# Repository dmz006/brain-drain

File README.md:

# brain-drain

A standalone disk sanitizer: plug a drive in, it gets wiped to NIST SP 800-88 Rev. 2 and you get a certificate. No buttons, no
screen to poke at, no PC. A Raspberry Pi Compute Module 5 on a custom carrier board, plug-in bay cards (one per drive, up to eight, four
in version 1), an M.2 NVMe bay, a Python service and a 3D-printed enclosure that fits a backpack.

> **Status: design complete enough for layout review, nothing fabricated yet.** Both boards are routed with 0 DRC errors in KiCad, the
> software has 74 passing tests and the enclosure exports clean STLs. The boards have not been reviewed by a board designer and nothing has
> been simulated; the first bench test with a real drive is scheduled for 2026-09-26. See [docs/STATUS.md](docs/STATUS.md).
> **Handing this to an engineer? Start with [docs/LAYOUT-REVIEW.md](docs/LAYOUT-REVIEW.md).**

## What it does

* Up to eight SATA bays as plug-in cards (four fitted), each a USB 3 bridge
  with its own switched power. Drives are not docked: each bay is a 0.5 m
  22-pin SATA cable (data + power) that rises through the lid and plugs straight
  onto a bare 3.5" or 2.5" drive lying on the bench. Plus an M.2 NVMe bay under
  the lid (bay 9). Each bay is independent.
* Set the policy on an 8-way DIP switch. Plug a drive in: it is identified,
  wiped, verified and reported. Unplug it: the job aborts. That is the whole UI.
* Methods follow NIST 800-88 Rev. 2: single-pass overwrite with full
  verification for magnetic drives, firmware Sanitize (crypto or block erase)
  for SSDs and NVMe, legacy 3-pass and 7-pass available for those who insist.
* A JSON certificate per drive per job: what was attempted, what worked, how it
  was verified, and which tier (Clear / Purge) is honestly claimed.
* A 128×64 OLED shows per-bay progress and ETA. When idle it shows a QR code:
  scan it with a phone to join the unit's Wi-Fi, open the address, and you get
  the status page, the certificates to download, the log, and the option to
  join the unit to your own network. A key on the screen authorises changes.
  DIP mode 110 resets Wi-Fi (or everything, with DIP 8) without a network.

## Use cases

* IT refresh: wiping a pile of decommissioned laptop and desktop drives
  unattended, four at a time, with paperwork for each.
* Reselling or donating hardware where a Purge-level record is wanted.
* Small MSPs and repair shops that need a repeatable wipe without dedicating a PC.

## The hardware

|  |  |
|---|---|
| **Brain board**, 150 x 122 mm, six layers: CM5 wireless, two USB5744 hubs, eight PCIe-x1-style bay slots, M.2 socket, 12 V input and bucks, OLED, DIP switch | **Bay card**, 45 x 46 mm, four layers: ASM1153E USB 3 to SATA bridge, per-bay 12 V / 5 V power switch, SATA receptacle, PCIe x1 fingers |

More views, the case, the assembled unit, an exploded view, a cut-away and the complete system: [docs/RENDERS.md](docs/RENDERS.md).

## Repository layout

| Directory | Workstream | State |
|---|---|---|
| [`hardware/`](hardware/README.md) | KiCad 9 projects for the brain board and the bay card, generated from one netlist source; review pack, per-layer images, BOM | schematic clean; both boards routed, 0 open connections, 0 DRC errors, all differential pairs matched; **unreviewed, unsimulated, not fabricated** |
| [`software/`](software/README.md) | `braindrain` Python service, simulator, bench tool, Wi-Fi access point + phone page, Pi deployment | 74 tests, ready for the first bench |
| [`enclosure/`](enclosure/README.md) | OpenSCAD case, about 157 x 145 x 62 mm: tray, hinged lid with eight cable windows and a snap latch, OLED bezel; render gallery script | STLs export, renders done, not printed |
| [`docs/`](docs/README.md) | architecture, review guide, BOM, decisions, status, usage, diagrams, renders | |

## Quick start

```
# simulate the appliance on any Linux box
cd software && python3 -m venv .venv && . .venv/bin/activate && pip install -e ".[dev]"
braindrain simulate --grace 2            # terminal 1
braindrain sim-plug 1 --size 1G --prefill # terminal 2: a drive appears in bay 1 and is wiped

# regenerate a board from its source and route it unattended (BD_PROJECT=brain or card; see docs/USAGE.md)
cd hardware && python3 tools/symgen.py && BD_PROJECT=card python3 tools/gen_sch.py && BD_PROJECT=card sh tools/route_full.sh

# export the enclosure and render every image
cd enclosure && make && make renders
```

More in [docs/USAGE.md](docs/USAGE.md).

## Documentation

* **For the layout engineer: [Layout and design review guide](docs/LAYOUT-REVIEW.md)** · generated review data in [`hardware/review/`](hardware/review/)
* [Architecture](docs/ARCHITECTURE.md) · [System block diagram](docs/img/system-block.png) · [Renders and drawings](docs/RENDERS.md)
* [Bill of materials](docs/BOM.md) · [Fabrication and assembly vendors, cost estimate](docs/FABRICATION.md) · [Decisions](docs/DECISIONS.md)
* [Status and remaining work](docs/STATUS.md) · [Testing tracker](docs/testing-tracker.md)
* [Usage and regeneration](docs/USAGE.md) · [Bench plan for 2026-09-26](docs/saturday-bench-plan.md)
* [BRAIN-DRAIN-CONTEXT.md](BRAIN-DRAIN-CONTEXT.md) project context · [AGENT.md](AGENT.md) rules for agents and contributors · [CONTRIBUTING](CONTRIBUTING.md) · [CHANGELOG](CHANGELOG.md)

## Safety

This device destroys data by design. The software's safety fence only ever
targets whole disks behind an allow-listed USB bridge on a configured bay port,
or the M.2 slot, and never anything mounted or holding the root filesystem.
Treat every drive that touches a bay as gone.

## Licence

[Polyform Noncommercial 1.0.0](LICENSE): you may use, modify and share this
project for noncommercial purposes. Commercial use needs permission from the
author. Applies to the hardware sources, the software and the enclosure alike.

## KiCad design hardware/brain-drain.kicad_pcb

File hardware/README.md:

# hardware: the brain board and the bay card

Two KiCad 9 projects, both **generated** from `tools/design.py` (see [../docs/LAYOUT-REVIEW.md](../docs/LAYOUT-REVIEW.md) for how, and for what a
layout engineer must check). Design intent: [../docs/ARCHITECTURE.md](../docs/ARCHITECTURE.md) section 3. Parts: [../docs/BOM.md](../docs/BOM.md).
Regenerate and route commands: [../docs/USAGE.md](../docs/USAGE.md).

| | Brain board | Bay card |
|---|---|---|
| Project | `brain-drain.kicad_pro` | `bay-card/bay-card.kicad_pro` |
| Size, layers | 150 x 122 mm, 6 layers (F sig, In1 GND, In2 sig, In3 sig, In4 power, B sig), 1.6 mm, ENIG | 45 x 46 mm, 4 layers (F sig, In1 GND, In2 power, B sig), 1.6 mm, ENIG, finger tab |
| Contents | CM5 wireless, two USB5744 hubs, eight PCIe x1 bay slots, M.2 socket, 12 V input and bucks, OLED and DIP headers, LEDs, microSD, USB-C | ASM1153E bridge, two P-FET power switches with PTC fuses, SATA 22-pin receptacle, PCIe x1 fingers |
| Schematic sheets | `power-input`, `power-bucks`, `cm5`, `usb3-hub-A`, `usb3-hub-B`, `bay-slots`, `m2-nvme` | `bridge`, `bay-switch`, `edge` |
| Status | routed: 0 open connections, 0 DRC errors, 44 pairs matched | routed: 0 open connections, 0 DRC errors, 8 pairs matched |

More views and the assembled unit: [../docs/RENDERS.md](../docs/RENDERS.md). KiCad's own 3D views are in `renders/`, one image per layer in
`renders/layers/` (F.Cu, In1 to In4, B.Cu, assembly-top, assembly-bottom, mask), schematic sheets in `renders/schematic/`.

## Layout of this directory

```
hardware/
  brain-drain.kicad_pro / .kicad_sch / .kicad_pcb   the brain (generated; the PCB also carries the routing)
  sheets/*.kicad_sch                                7 brain sheets (generated)
  bay-card/                                         the bay card project, same layout: .kicad_pro/.sch/.pcb, sheets/, routing/, renders/
  CONNECTIONS.md, bay-card/CONNECTIONS.md           net-by-net connection lists (generated)
  lib/brain-drain.kicad_sym, lib/brain-drain.pretty custom symbols and footprints (see lib/brain-drain.pretty/README.md for origins)
  review/                                           generated review pack: design rules, stack-up, planes, keep-outs, routing statistics,
                                                    DRC / ERC summaries, footprint provenance, netlists, placement CSV, schematic PDFs
  routing/, bay-card/routing/                       Specctra DSN/SES for freerouting, drc.json, open.md, pairs.md, chain.log
  renders/, bay-card/renders/                       KiCad 3D views, per-layer PNGs, schematic PNGs and PDFs
  bom/                                              brain-drain-bom.csv, bay-card-bom.csv (generated)
  ref/                                              pin tables (CSV), DOWNLOADS.md; ref/datasheets/ is gitignored
  tools/                                            the generators and the routing pipeline, listed in ../docs/LAYOUT-REVIEW.md section 6
  fab/                                              fab/<date>/ order packs (gitignored)
```

## Board rules

* Design rules follow the Raspberry Pi CM5IO reference: 0.13 mm tracks, 0.125 mm clearance, 0.45/0.2 mm vias, 0.3 mm copper to the board edge,
  0.2 mm hole clearance; power nets 0.3 mm tracks with 0.6/0.3 mm vias; 0.3/0.15 mm vias for the 0.4 mm-pitch QFN supply pins only (D8, confirm
  with the fab). They are written into each project file by `route.py prepare`; the table is in `review/design-rules.md`.
* Differential pairs: 90 ohm (USB 3, SATA, USB 2), 85 ohm (PCIe). The class `DiffPair90` is 0.147 mm / 0.253 mm gap, **carried over from a four-layer
  design and not yet recalculated for the six-layer stack-up**. Pairs are length-matched end to end (across the series capacitors) to 0.15 mm.
* CM5 antenna strip: no copper on any layer and no parts (rule area `keepout_CM5_antenna`); keep-outs around the CM5's four standoff holes.
* CM5 boot-order straps: eMMC/SD only. All bay power switches default **off** (10 k pull-down on `BAY_EN`, on the card).
* Input: 4-pin DIN (Kycon KPJX-4S-S); the pin assignment must match the chosen brick.

## Before fabrication

See [../docs/LAYOUT-REVIEW.md](../docs/LAYOUT-REVIEW.md) (priority items and the sign-off checklist) and [../docs/STATUS.md](../docs/STATUS.md) R2, R3, R10, R25 to R30:
the stack-up and pair geometry, the M.2 footprint against the TE drawing, the Molex face position, the DIN pinout from the chosen brick, test points, fiducials
and ESD, the card panel.

## Bench validation that does not need these boards

Any Linux box plus an ASM1153E-based USB dock answers the risky questions: does `hdparm --sanitize-*` pass through, does the bridge survive a long SECURITY ERASE,
does `--sanitize-status` report progress. A Pi 5 with two docks is the exact software test bed for this topology. Do this first
([../docs/saturday-bench-plan.md](../docs/saturday-bench-plan.md)).

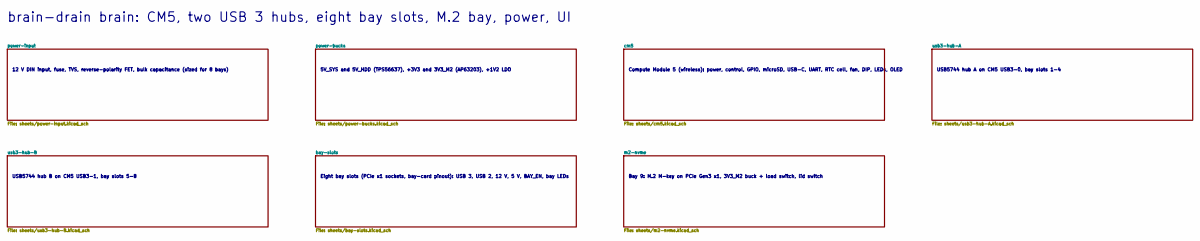
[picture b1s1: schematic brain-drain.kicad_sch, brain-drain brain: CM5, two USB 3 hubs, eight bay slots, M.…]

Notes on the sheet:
brain-drain brain: CM5, two USB 3 hubs, eight bay slots, M.2 bay, power, UI
12 V DIN input, fuse, TVS, reverse-polarity FET, bulk capacitance (sized for 8 bays)
5V_SYS and 5V_HDD (TPS56637), +3V3 and 3V3_M2 (AP63203), +1V2 LDO
Compute Module 5 (wireless): power, control, GPIO, microSD, USB-C, UART, RTC cell, fan, DIP, LEDs, OLED
USB5744 hub A on CM5 USB3-0, bay slots 1-4
USB5744 hub B on CM5 USB3-1, bay slots 5-8
Eight bay slots (PCIe x1 sockets, bay-card pinout): USB 3, USB 2, 12 V, 5 V, BAY_EN, bay LEDs
Bay 9: M.2 M-key on PCIe Gen3 x1, 3V3_M2 buck + load switch, lid switch

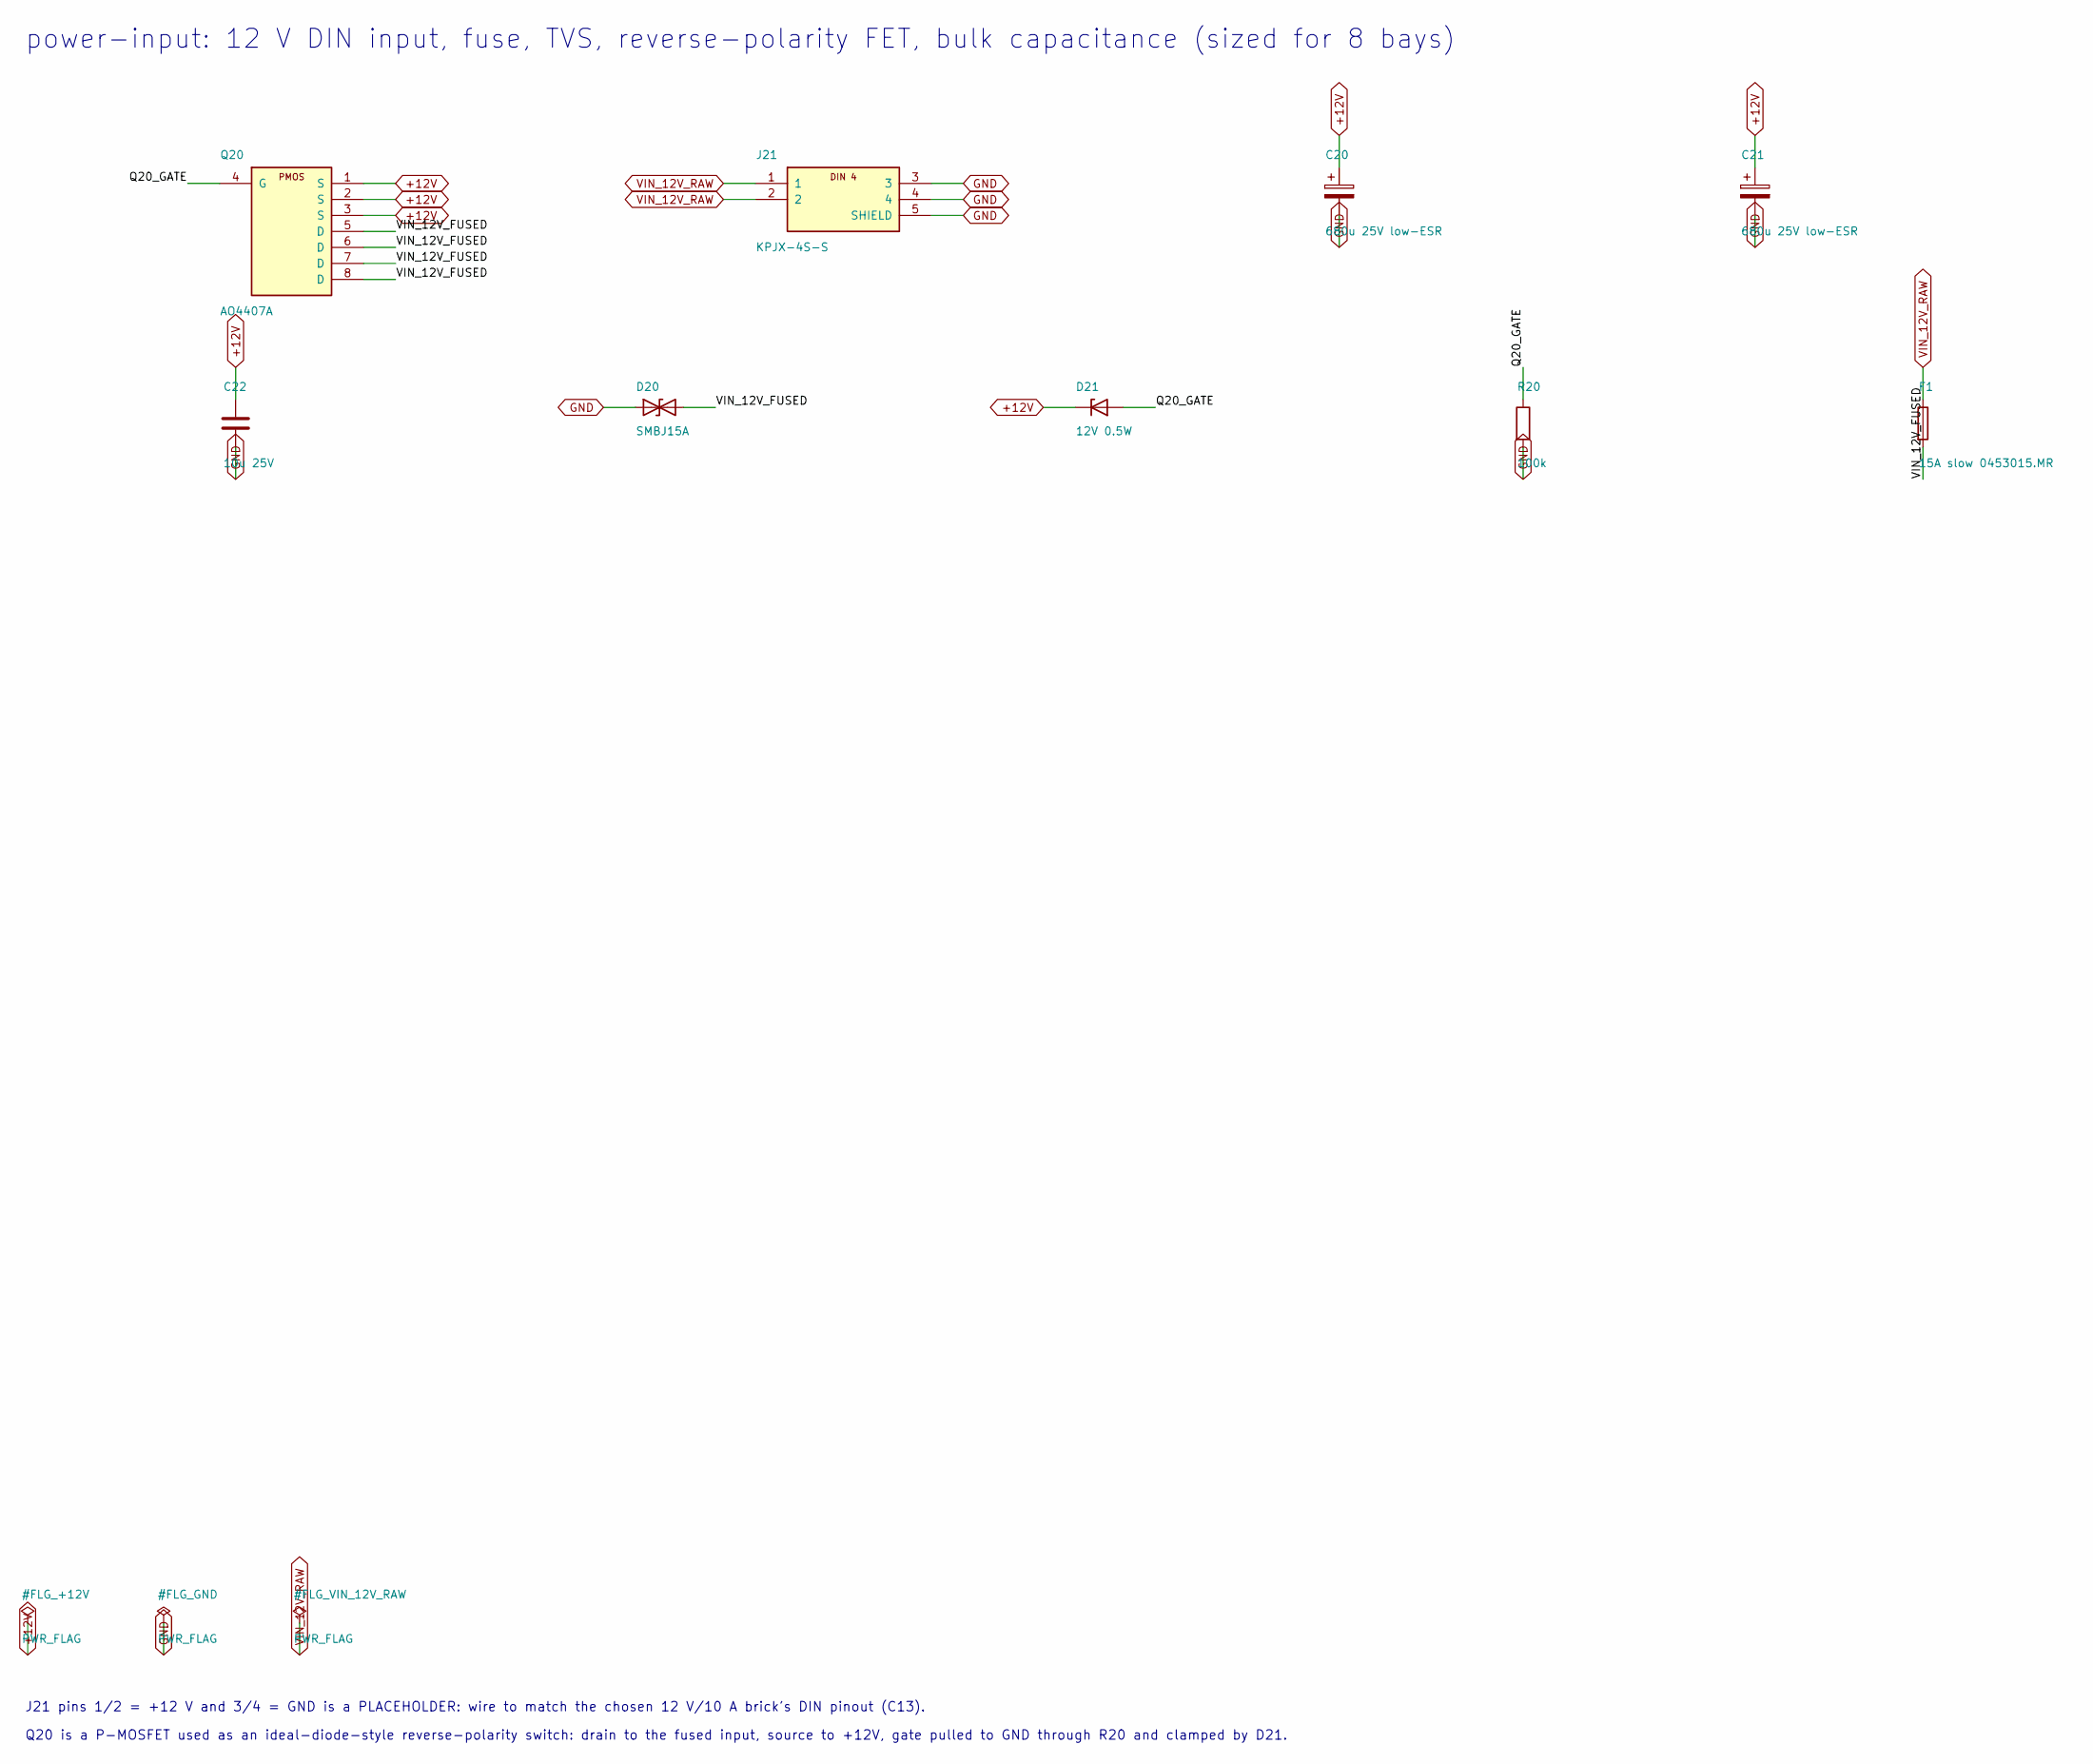
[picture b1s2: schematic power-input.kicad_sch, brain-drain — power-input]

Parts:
C20, C21: 680u 25V low-ESR; CP_Elec_10x10.5
C22: 10u 25V; C_1210_3225Metric
D20: SMBJ15A; D_SMB
D21: 12V 0.5W; D_SOD-123
F1: 15A slow 0453015.MR; Fuse_Littelfuse-NANO2-451_453
J21: KPJX-4S-S; Kycon_KPJX-4S-S
Q20: AO4407A; SOIC-8_3.9x4.9mm_P1.27mm
R20: 100k; R_0603_1608Metric

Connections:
+12V: C20.1, C21.1, C22.1, D21.1 (K), Q20.1 (S), Q20.2 (S), Q20.3 (S); also elsewhere on the board
GND: C20.2, C21.2, C22.2, D20.1 (A1), J21.3, J21.4, J21.5 (SHIELD), R20.2; also elsewhere on the board
Q20_GATE: D21.2 (A), Q20.4 (G), R20.1
VIN_12V_FUSED: D20.2 (A2), F1.2, Q20.5 (D), Q20.6 (D), Q20.7 (D), Q20.8 (D)
VIN_12V_RAW: F1.1, J21.1, J21.2

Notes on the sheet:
power-input: 12 V DIN input, fuse, TVS, reverse-polarity FET, bulk capacitance (sized for 8 bays)
J21 pins 1/2 = +12 V and 3/4 = GND is a PLACEHOLDER: wire to match the chosen 12 V/10 A brick's DIN pinout (C13).
Q20 is a P-MOSFET used as an ideal-diode-style reverse-polarity switch: drain to the fused input, source to +12V, gate pulled to GND through R20 and clamped by D21.

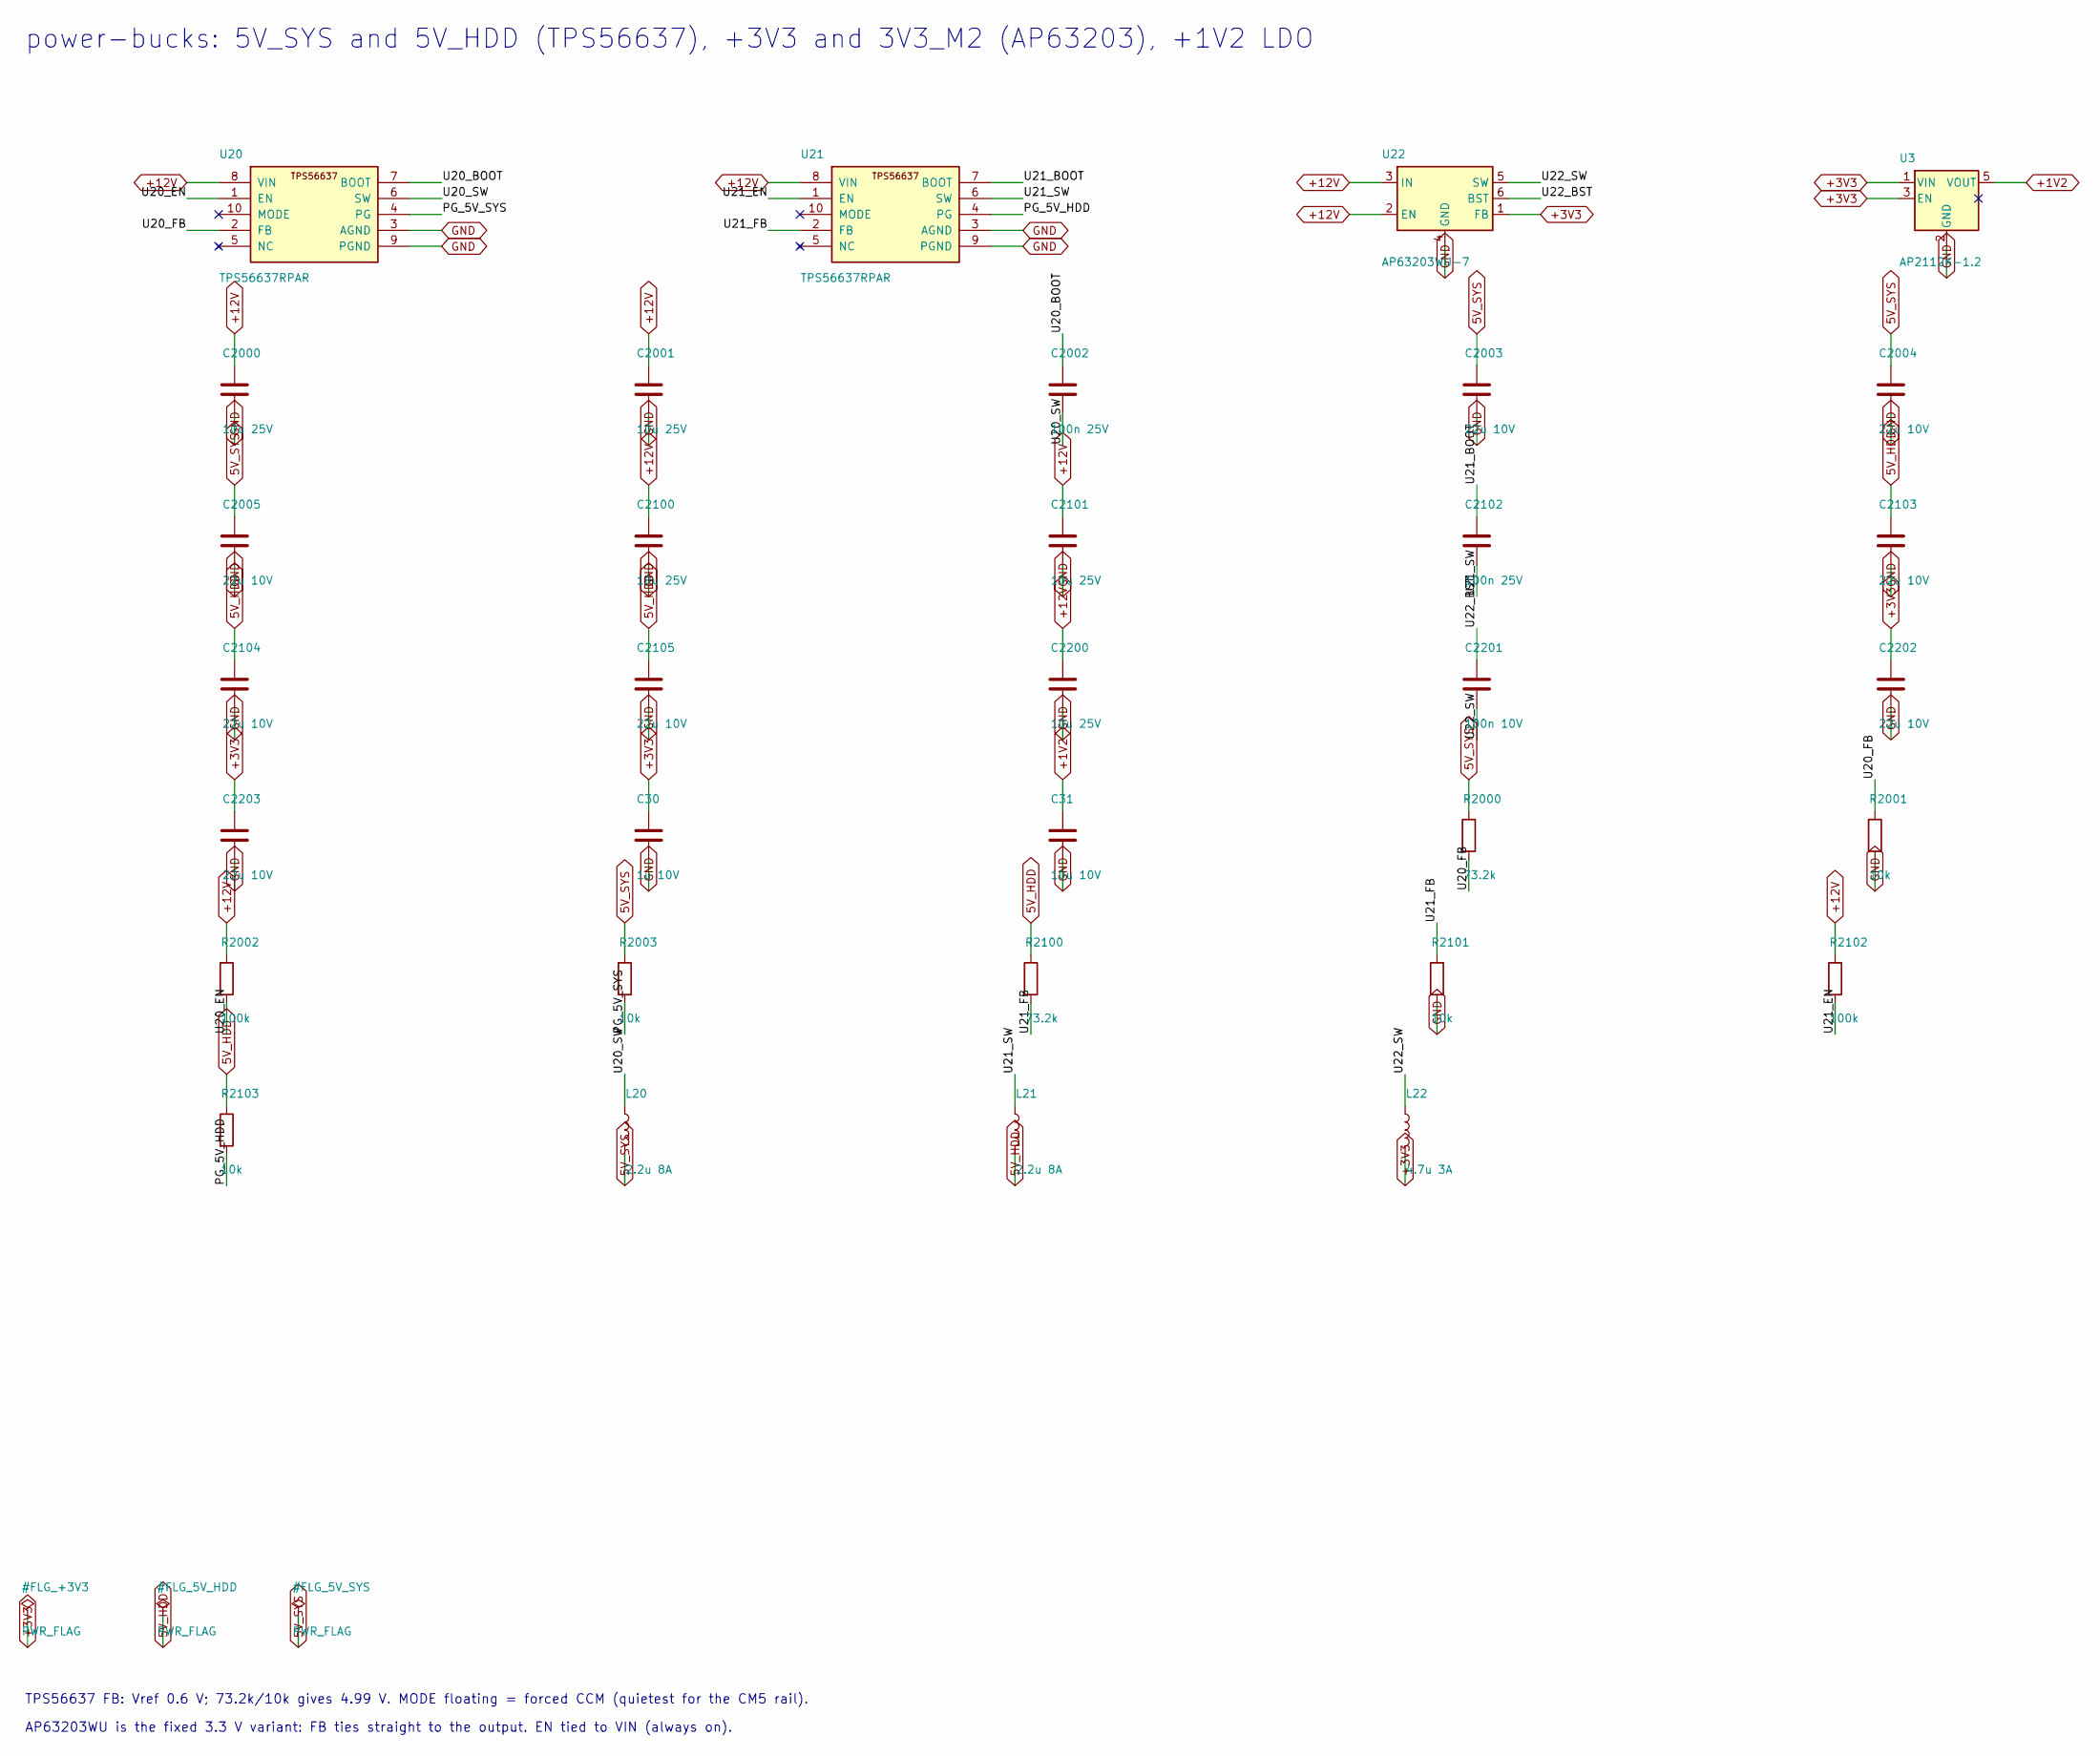
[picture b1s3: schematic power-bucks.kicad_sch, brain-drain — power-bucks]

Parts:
C30: 1u 10V; C_0402_1005Metric
C31: 10u 10V; C_0805_2012Metric
C2000, C2001, C2100, C2101, C2200: 10u 25V; C_1210_3225Metric
C2002, C2102: 100n 25V; C_0402_1005Metric
C2003, C2004, C2005, C2103, C2104, C2105, C2202, C2203: 22u 10V; C_0805_2012Metric
C2201: 100n 10V; C_0402_1005Metric
L20, L21: 2.2u 8A; L_Taiyo-Yuden_NR-60xx
L22: 4.7u 3A; L_Taiyo-Yuden_NR-40xx
R2000, R2100: 73.2k; R_0402_1005Metric
R2001, R2003, R2101, R2103: 10k; R_0402_1005Metric
R2002, R2102: 100k; R_0402_1005Metric
U3: AP2112K-1.2; SOT-23-5
U20, U21: TPS56637RPAR; Texas_RPA0010A_VQFN-HR-10_3x3mm
U22: AP63203WU-7; TSOT-23-6

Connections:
5V_HDD: C2103.1, C2104.1, C2105.1, L21.2, R2100.1, R2103.1; also elsewhere on the board
5V_SYS: C2003.1, C2004.1, C2005.1, L20.2, R2000.1, R2003.1; also elsewhere on the board
+1V2: C31.1, U3.5 (VOUT); also elsewhere on the board
+3V3: C30.1, C2202.1, C2203.1, L22.2, U3.1 (VIN), U3.3 (EN), U22.1 (FB); also elsewhere on the board
+12V: C2000.1, C2001.1, C2100.1, C2101.1, C2200.1, R2002.1, R2102.1, U20.8 (VIN), U21.8 (VIN), U22.2 (EN), U22.3 (IN); also elsewhere on the board
GND: C30.2, C31.2, C2000.2, C2001.2, C2003.2, C2004.2, C2005.2, C2100.2, C2101.2, C2103.2, C2104.2, C2105.2, C2200.2, C2202.2, C2203.2, R2001.2, R2101.2, U3.2 (GND), U20.3 (AGND), U20.9 (PGND), U21.3 (AGND), U21.9 (PGND), U22.4 (GND); also elsewhere on the board
PG_5V_HDD: R2103.2, U21.4 (PG)
PG_5V_SYS: R2003.2, U20.4 (PG)
U20_BOOT: C2002.1, U20.7 (BOOT)
U20_EN: R2002.2, U20.1 (EN)
U20_FB: R2000.2, R2001.1, U20.2 (FB)
U20_SW: C2002.2, L20.1, U20.6 (SW)
U21_BOOT: C2102.1, U21.7 (BOOT)
U21_EN: R2102.2, U21.1 (EN)
U21_FB: R2100.2, R2101.1, U21.2 (FB)
U21_SW: C2102.2, L21.1, U21.6 (SW)
U22_BST: C2201.1, U22.6 (BST)
U22_SW: C2201.2, L22.1, U22.5 (SW)

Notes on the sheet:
power-bucks: 5V_SYS and 5V_HDD (TPS56637), +3V3 and 3V3_M2 (AP63203), +1V2 LDO
TPS56637 FB: Vref 0.6 V; 73.2k/10k gives 4.99 V. MODE floating = forced CCM (quietest for the CM5 rail).
AP63203WU is the fixed 3.3 V variant: FB ties straight to the output. EN tied to VIN (always on).

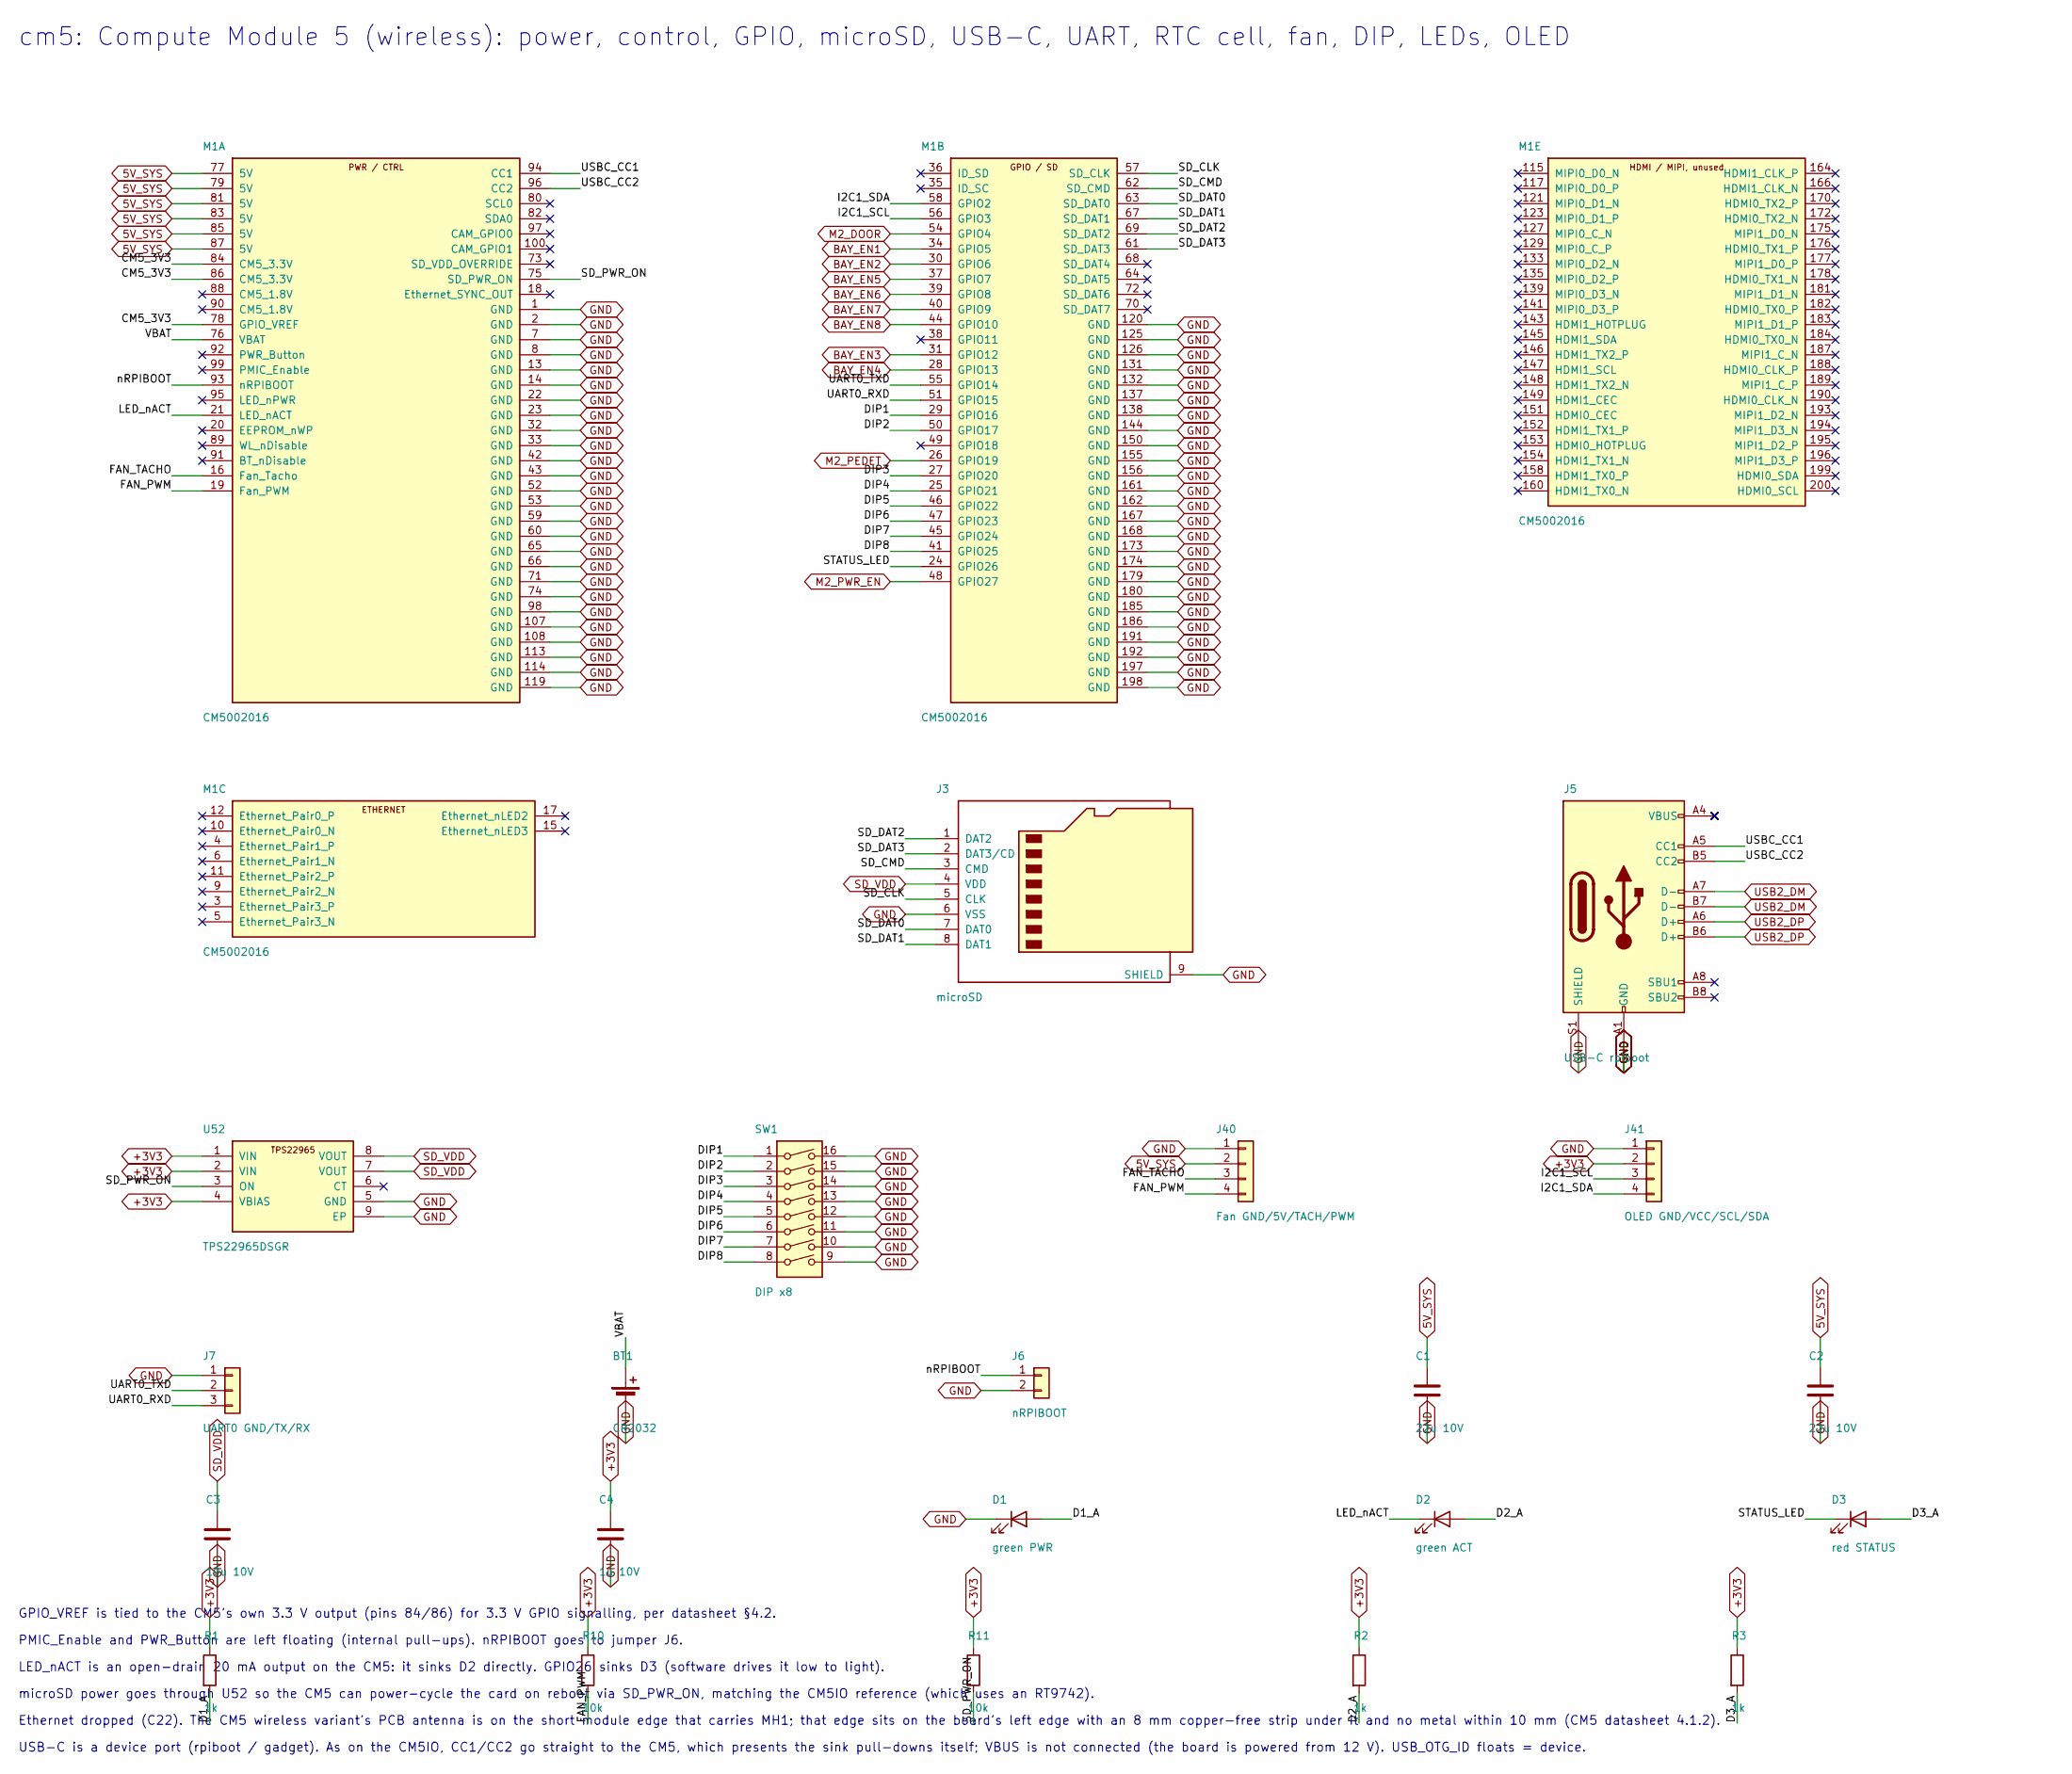
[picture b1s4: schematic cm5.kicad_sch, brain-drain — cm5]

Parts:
BT1: CR2032; BatteryHolder_Keystone_1060_1x2032
C1, C2: 22u 10V; C_0805_2012Metric
C3: 10u 10V; C_0805_2012Metric
C4: 1u 10V; C_0402_1005Metric
D1: green PWR; LED_D3.0mm
D2: green ACT; LED_D3.0mm
D3: red STATUS; LED_D3.0mm
J3: microSD; microSD_HC_Hirose_DM3AT-SF-PEJM5
J5: USB-C rpiboot; USB_C_Receptacle_GCT_USB4085
J6: nRPIBOOT; PinHeader_1x02_P2.54mm_Vertical
J7: UART0 GND/TX/RX; PinHeader_1x03_P2.54mm_Vertical
J40: Fan GND/5V/TACH/PWM; FanPinHeader_1x04_P2.54mm_Vertical
J41: OLED GND/VCC/SCL/SDA; PinHeader_1x04_P2.54mm_Vertical
M1: CM5002016; Raspberry-Pi-5-Compute-Module
R1, R2, R3: 1k; R_0603_1608Metric
R10, R11: 10k; R_0402_1005Metric
SW1: DIP x8; SW_DIP_SPSTx08_Piano_10.8x21.88mm_W7.62mm_P2.54mm
U52: TPS22965DSGR; Texas_DSG0008A_WSON-8-1EP_2x2mm_P0.5mm_EP0.9x1.6mm

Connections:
5V_SYS: C1.1, C2.1, J40.2, M1.77 (5V), M1.79 (5V), M1.81 (5V), M1.83 (5V), M1.85 (5V), M1.87 (5V); also elsewhere on the board
+3V3: C4.1, J41.2, R1.1, R2.1, R3.1, R10.1, R11.1, U52.1 (VIN), U52.2 (VIN), U52.4 (VBIAS); also elsewhere on the board
BAY_EN1: M1.34 (GPIO5); also elsewhere on the board
BAY_EN2: M1.30 (GPIO6); also elsewhere on the board
BAY_EN3: M1.31 (GPIO12); also elsewhere on the board
BAY_EN4: M1.28 (GPIO13); also elsewhere on the board
BAY_EN5: M1.37 (GPIO7); also elsewhere on the board
BAY_EN6: M1.39 (GPIO8); also elsewhere on the board
BAY_EN7: M1.40 (GPIO9); also elsewhere on the board
BAY_EN8: M1.44 (GPIO10); also elsewhere on the board
CM5_3V3: M1.78 (GPIO_VREF), M1.84 (CM5_3.3V), M1.86 (CM5_3.3V)
D1_A: D1.2 (A), R1.2
D2_A: D2.2 (A), R2.2
D3_A: D3.2 (A), R3.2
DIP1: M1.29 (GPIO16), SW1.1
DIP2: M1.50 (GPIO17), SW1.2
DIP3: M1.27 (GPIO20), SW1.3
DIP4: M1.25 (GPIO21), SW1.4
DIP5: M1.46 (GPIO22), SW1.5
DIP6: M1.47 (GPIO23), SW1.6
DIP7: M1.45 (GPIO24), SW1.7
DIP8: M1.41 (GPIO25), SW1.8
FAN_PWM: J40.4, M1.19 (Fan_PWM), R10.2
FAN_TACHO: J40.3, M1.16 (Fan_Tacho)
GND: BT1.2 (-), C1.2, C2.2, C3.2, C4.2, D1.1 (K), J3.6 (VSS), J3.9 (SHIELD), J5.A1 (GND), J5.A12 (GND), J5.B1 (GND), J5.B12 (GND), J5.S1 (SHIELD), J6.2, J7.1, J40.1, J41.1, M1.1 (GND), M1.2 (GND), M1.7 (GND), M1.8 (GND), M1.13 (GND), M1.14 (GND), M1.22 (GND), M1.23 (GND), M1.32 (GND), M1.33 (GND), M1.42 (GND), M1.43 (GND), M1.52 (GND), M1.53 (GND), M1.59 (GND), M1.60 (GND), M1.65 (GND), M1.66 (GND), M1.71 (GND), M1.74 (GND), M1.98 (GND), M1.107 (GND), M1.108 (GND), M1.113 (GND), M1.114 (GND), M1.119 (GND), M1.120 (GND), M1.125 (GND), M1.126 (GND), M1.131 (GND), M1.132 (GND), M1.137 (GND), M1.138 (GND), M1.144 (GND), M1.150 (GND), M1.155 (GND), M1.156 (GND), M1.161 (GND), M1.162 (GND), M1.167 (GND), M1.168 (GND), M1.173 (GND), M1.174 (GND), M1.179 (GND), M1.180 (GND), M1.185 (GND), M1.186 (GND), M1.191 (GND), M1.192 (GND), M1.197 (GND), M1.198 (GND), SW1.9, SW1.10, SW1.11, SW1.12, SW1.13, SW1.14, SW1.15, SW1.16, U52.5 (GND), U52.9 (EP); also elsewhere on the board
I2C1_SCL: J41.3, M1.56 (GPIO3)
I2C1_SDA: J41.4, M1.58 (GPIO2)
LED_nACT: D2.1 (K), M1.21 (LED_nACT)
M2_DOOR: M1.54 (GPIO4); also elsewhere on the board
M2_PEDET: M1.26 (GPIO19); also elsewhere on the board
M2_PWR_EN: M1.48 (GPIO27); also elsewhere on the board
SD_CLK: J3.5 (CLK), M1.57 (SD_CLK)
SD_CMD: J3.3 (CMD), M1.62 (SD_CMD)
SD_DAT0: J3.7 (DAT0), M1.63 (SD_DAT0)
SD_DAT1: J3.8 (DAT1), M1.67 (SD_DAT1)
SD_DAT2: J3.1 (DAT2), M1.69 (SD_DAT2)
SD_DAT3: J3.2 (DAT3/CD), M1.61 (SD_DAT3)
SD_PWR_ON: M1.75 (SD_PWR_ON), R11.2, U52.3 (ON)
SD_VDD: C3.1, J3.4 (VDD), U52.7 (VOUT), U52.8 (VOUT)
STATUS_LED: D3.1 (K), M1.24 (GPIO26)
UART0_RXD: J7.3, M1.51 (GPIO15)
UART0_TXD: J7.2, M1.55 (GPIO14)
USB2_DM: J5.A7 (D-), J5.B7 (D-); also elsewhere on the board
USB2_DP: J5.A6 (D+), J5.B6 (D+); also elsewhere on the board
USBC_CC1: J5.A5 (CC1), M1.94 (CC1)
USBC_CC2: J5.B5 (CC2), M1.96 (CC2)
VBAT: BT1.1 (+), M1.76 (VBAT)
nRPIBOOT: J6.1, M1.93 (nRPIBOOT)

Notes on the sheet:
cm5: Compute Module 5 (wireless): power, control, GPIO, microSD, USB-C, UART, RTC cell, fan, DIP, LEDs, OLED
GPIO_VREF is tied to the CM5's own 3.3 V output (pins 84/86) for 3.3 V GPIO signalling, per datasheet §4.2.
PMIC_Enable and PWR_Button are left floating (internal pull-ups). nRPIBOOT goes to jumper J6.
LED_nACT is an open-drain 20 mA output on the CM5: it sinks D2 directly. GPIO26 sinks D3 (software drives it low to light).
microSD power goes through U52 so the CM5 can power-cycle the card on reboot via SD_PWR_ON, matching the CM5IO reference (which uses an RT9742).
Ethernet dropped (C22). The CM5 wireless variant's PCB antenna is on the short module edge that carries MH1; that edge sits on the board's left edge with an 8 mm copper-free strip under it and no metal within 10 mm (CM5 datasheet 4.1.2).
USB-C is a device port (rpiboot / gadget). As on the CM5IO, CC1/CC2 go straight to the CM5, which presents the sink pull-downs itself; VBUS is not connected (the board is powered from 12 V). USB_OTG_ID floats = device.
